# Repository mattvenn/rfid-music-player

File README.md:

# rfid music player

## components

* teensy 3.2
* adafruit i2s amp
* rfid rc522 reader
* sd card breakout
* string of leds - currently ws2812, but need to switch to a clocked version for
 compatibility with audio library.

## pin allocations

    teensy          i/o
    6               led data out
    7               mosi sd and rfid reader
    9               i2s bclk
    10              cs sd card
    12              miso sd and rfid

    14              sck sd and rfid
    15              rfid cs
    16              rfid reset
    21 (A7)         vol pot in
    22              i2s din
    23              i2s lrc

    3.3v            rfid psu and positive vol pot
    vin (5v)        i2s amp psu, led string +5v

## sd pinout

    1           n/c
    2           cs
    3           mosi    
    4           3.3v
    5           clk
    6           gnd
    7           miso
    8           n/c

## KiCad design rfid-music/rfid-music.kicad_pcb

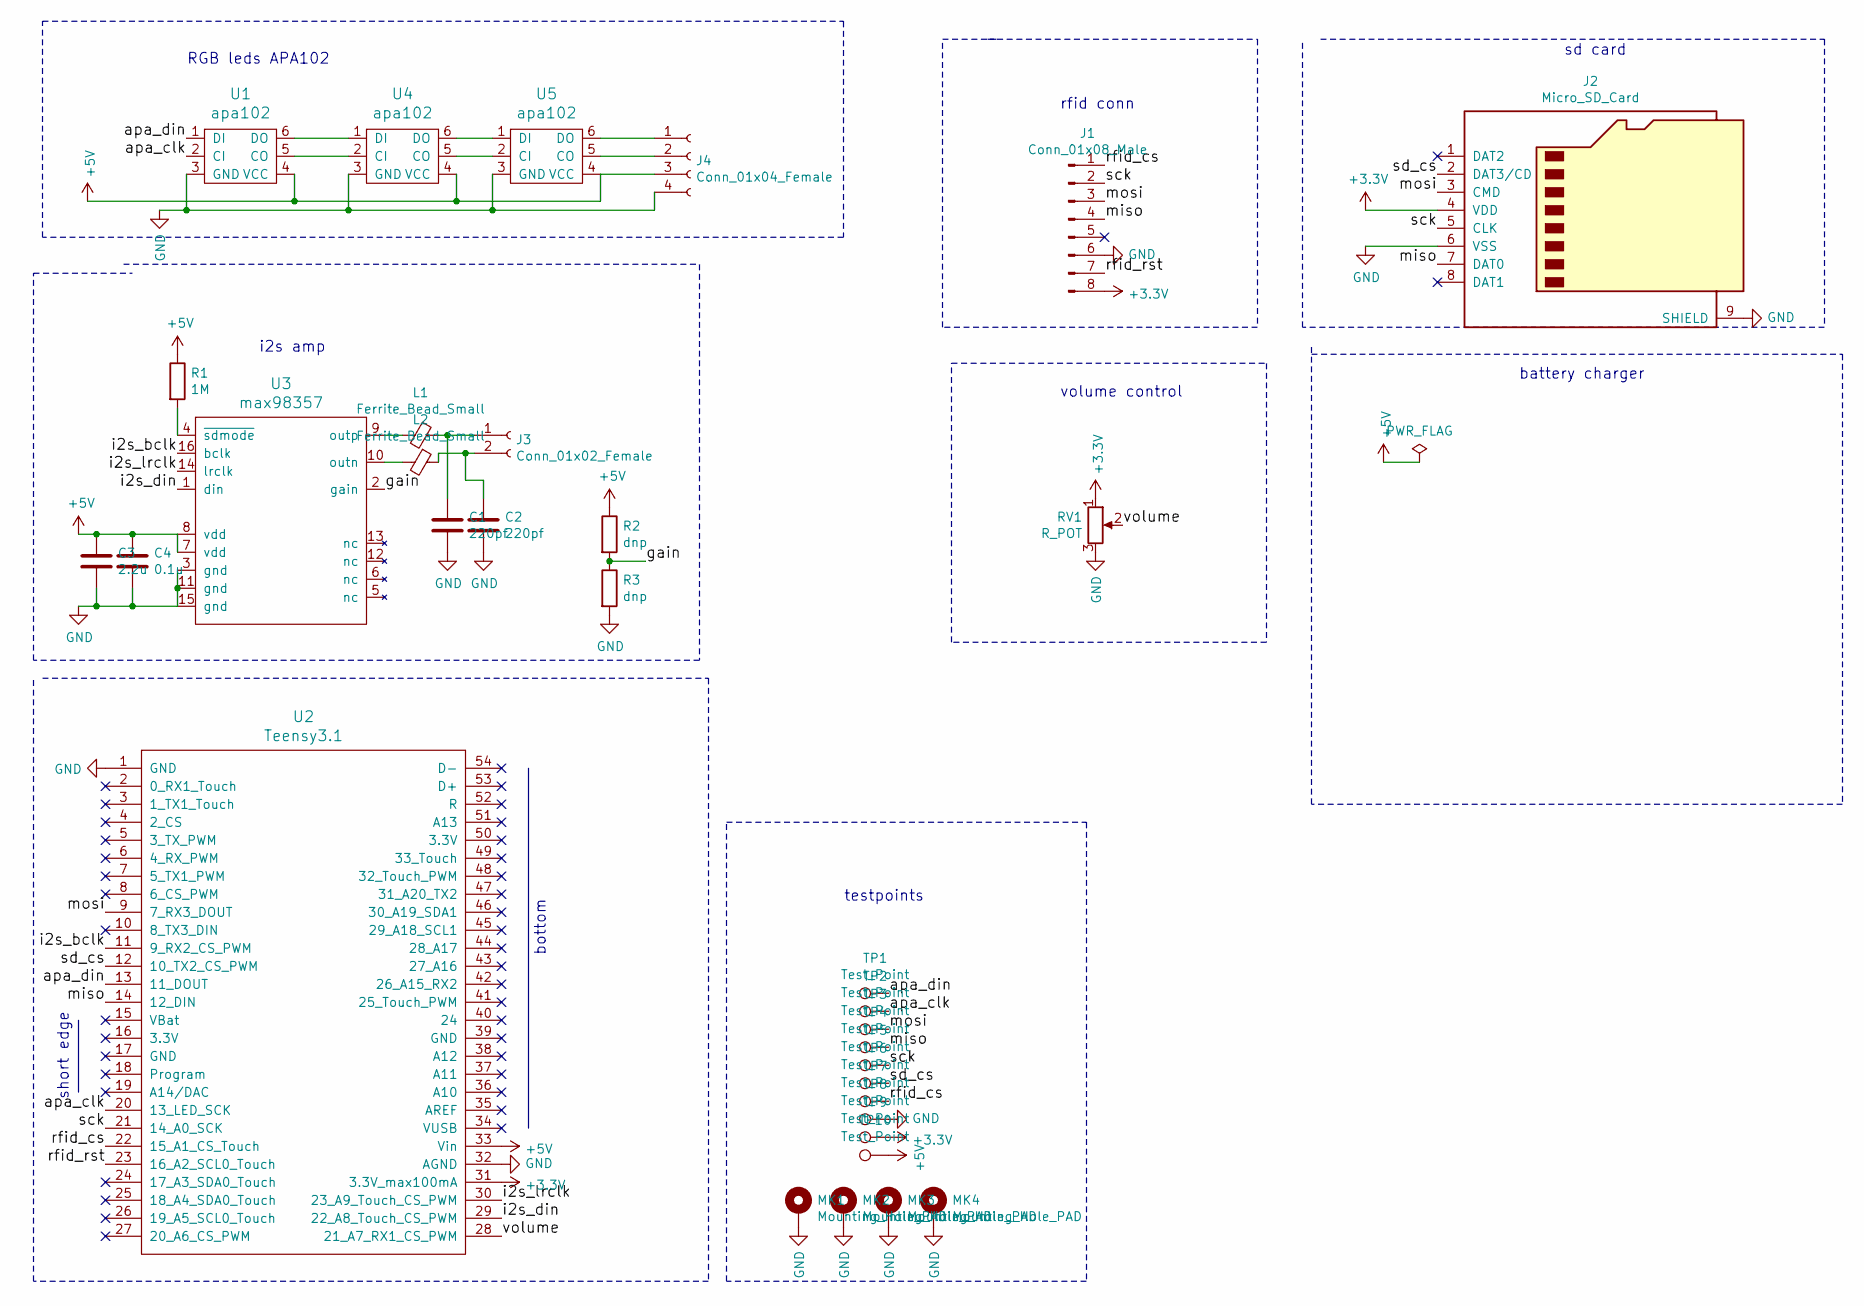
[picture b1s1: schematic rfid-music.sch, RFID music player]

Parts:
C1, C2: 220pf; C_0805_2012Metric
C3: 2.2u; C_0805_2012Metric
C4: 0.1u; C_0805_2012Metric
J1: Conn_01x08_Male; PinHeader_1x08_P2.54mm_Vertical
J2: Micro_SD_Card; microSD_HC_Hirose_DM3D-SF; farnell # 1764377
J3: Conn_01x02_Female; PinHeader_1x02_P2.54mm_Vertical
J4: Conn_01x04_Female; PinHeader_1x04_P2.54mm_Vertical
L1, L2: Ferrite_Bead_Small; L_0805_2012Metric
MK1, MK2, MK3, MK4: Mounting_Hole_PAD; MountingHole_3.2mm_M3_Pad
R1: 1M; R_0805_2012Metric
R2, R3: dnp; R_0805_2012Metric
RV1: R_POT; Potentiometer_Bourns_3314S_Horizontal; farnell # 1696070
TP1, TP2, TP3, TP4, TP5, TP6, TP7, TP8, TP9, TP10: Test_Point; Pin_D0.7mm_L6.5mm_W1.8mm_FlatFork
U1, U4, U5: apa102
U2: Teensy3.1; teensy31
U3: max98357; QFN-16-1EP_3x3mm_P0.5mm_EP2.7x2.7mm_ThermalVias

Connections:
+3V3: J1.8, J2.4 (VDD), RV1.1, TP9.1, U2.31 (3.3V_max100mA)
+5V: C3.1, C4.1, J4.3, R1.1, R2.1, TP10.1, U1.4 (VCC), U2.33 (Vin), U3.7 (vdd), U3.8 (vdd), U4.4 (VCC), U5.4 (VCC)
/apa_clk: TP2.1, U1.2 (CI), U2.20 (13_LED_SCK)
/apa_din: TP1.1, U1.1 (DI), U2.13 (11_DOUT)
/gain: R2.2, R3.1, U3.2 (gain)
/i2s_bclk: U2.11 (9_RX2_CS_PWM), U3.16 (bclk)
/i2s_din: U2.29 (22_A8_Touch_CS_PWM), U3.1 (din)
/i2s_lrclk: U2.30 (23_A9_Touch_CS_PWM), U3.14 (lrclk)
/miso: J1.4, J2.7 (DAT0), TP4.1, U2.14 (12_DIN)
/mosi: J1.3, J2.3 (CMD), TP3.1, U2.9 (7_RX3_DOUT)
/rfid_cs: J1.1, TP7.1, U2.22 (15_A1_CS_Touch)
/rfid_rst: J1.7, U2.23 (16_A2_SCL0_Touch)
/sck: J1.2, J2.5 (CLK), TP5.1, U2.21 (14_A0_SCK)
/sd_cs: J2.2 (DAT3/CD), TP6.1, U2.12 (10_TX2_CS_PWM)
/volume: RV1.2, U2.28 (21_A7_RX1_CS_PWM)
GND: C1.2, C2.2, C3.2, C4.2, J1.6, J2.6 (VSS), J2.9 (SHIELD), J4.4, MK1.1, MK2.1, MK3.1, MK4.1, R3.2, RV1.3, TP8.1, U1.3 (GND), U2.1 (GND), U2.32 (AGND), U3.3 (gnd), U3.11 (gnd), U3.15 (gnd), U4.3 (GND), U5.3 (GND)
unnamed: C1.1, J3.1, L1.1
unnamed: C2.1, J3.2, L2.1
unnamed: J4.1, U5.6 (DO)
unnamed: J4.2, U5.5 (CO)
unnamed: L1.2, U3.9 (outp)
unnamed: L2.2, U3.10 (outn)
unnamed: R1.2, U3.4 (~sdmode)
unnamed: U1.5 (CO), U4.2 (CI)
unnamed: U1.6 (DO), U4.1 (DI)
unnamed: U4.5 (CO), U5.2 (CI)
unnamed: U4.6 (DO), U5.1 (DI)

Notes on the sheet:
bottom
short edge
rfid conn
sd card
i2s amp
RGB leds APA102
volume control
battery charger
testpoints

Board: 2 copper layers, 33 parts (0 on the bottom side), 27 nets, no tracks yet.

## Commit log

2018-03-01 switched to better spi reader: rc522
2018-03-01 working fsm implementation
2018-03-01 uses index.txt to store rfid number to directory mapping
2018-03-02 status with leds
2018-03-02 volume control added with a mixer
2018-03-02 tweaks in leds
2018-03-02 comment and remove serial print vol
2018-03-03 pinout added to readme
2018-03-03 added SD card pinout
2018-03-03 reduced number of leds to improve led reliability
2018-03-03 ws2812 notes on reliability
2018-10-02 first commit on pcbs
